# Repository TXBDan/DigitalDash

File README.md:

# DigitalDash

This is a prototype digital dashboard for use in motorsports. I made it in 2015 and successfully ran it in my track car for a couple years. I'm now archiving the project here.

It features:
* LPC4088 microcontroller
* Many-LED RGB sequential shift light
* 20x4 character LCD display
* 2 LEDs (power/status and alarm)
* 3 push buttons (change screen, select, option)
* 4 analog inputs (water temp, oil temp, oil pressure, throttle position)
* 2 speed/pulse inputs (speed and tach)
* 10Hz GPS (position and elevation)
* 3-axis accelerometer
* SDcard logging

For a lot more info, check out the blog here: https://projectsofdan.com/?cat=18

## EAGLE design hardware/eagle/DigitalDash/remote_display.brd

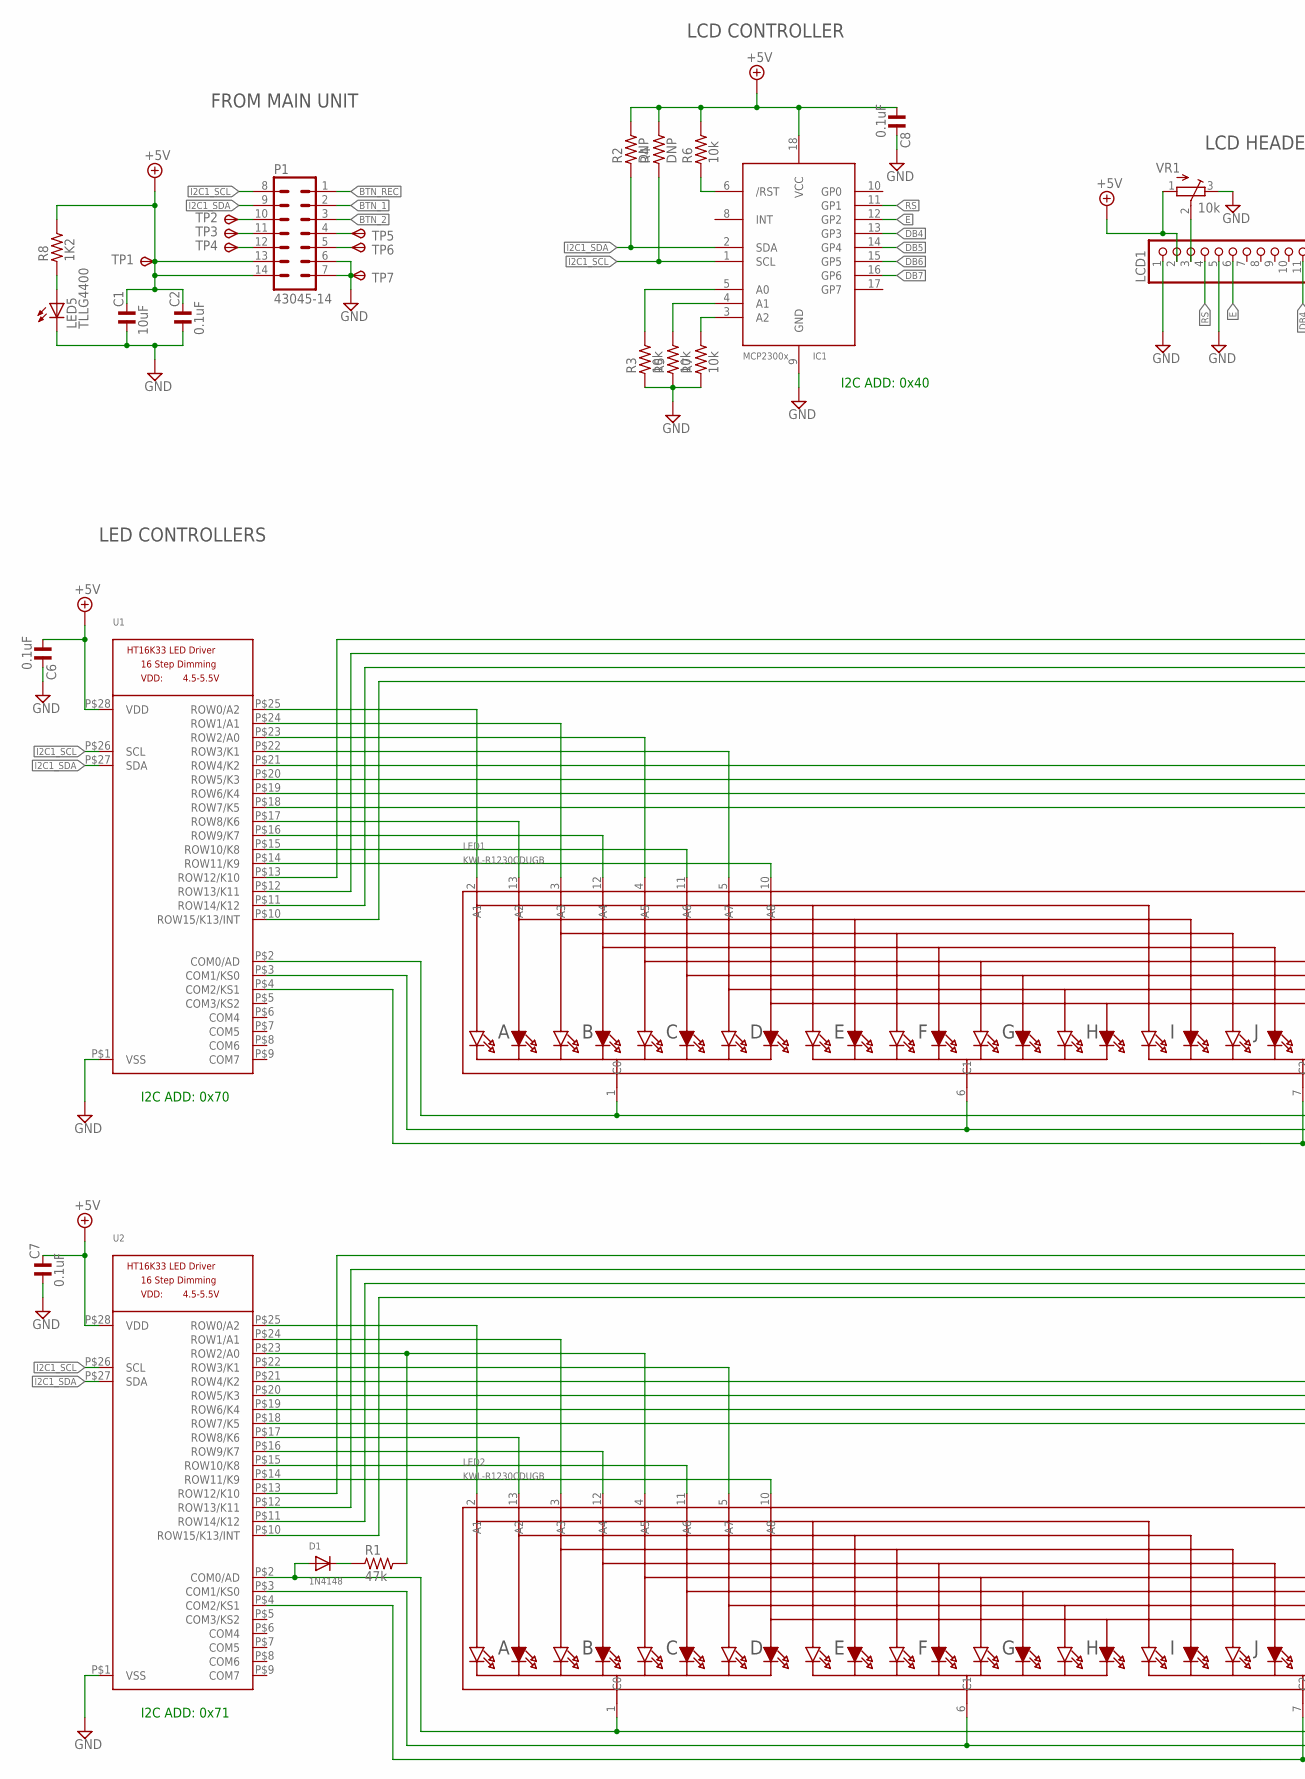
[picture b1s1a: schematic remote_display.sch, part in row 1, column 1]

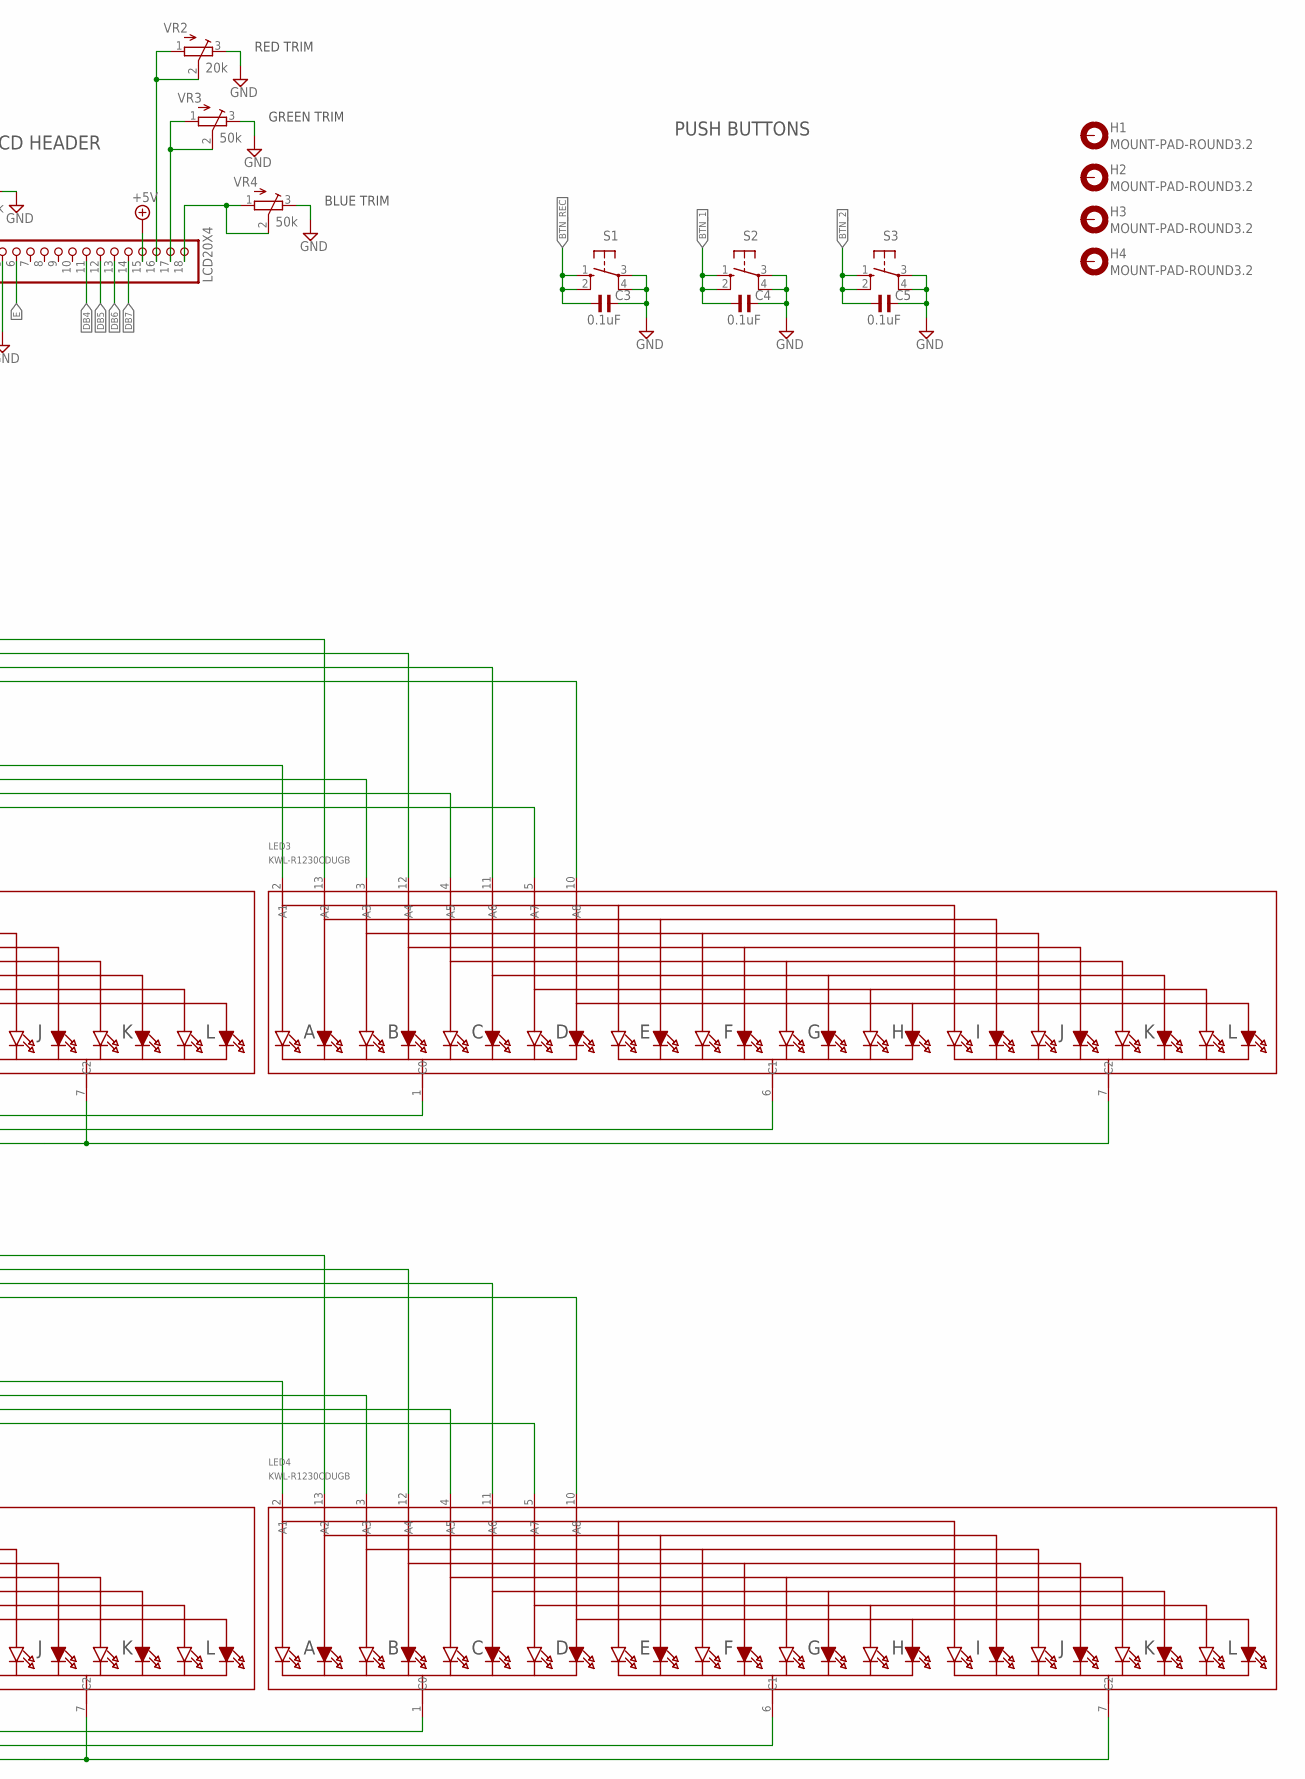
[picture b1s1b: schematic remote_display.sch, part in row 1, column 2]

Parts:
C1: 10uF; C0805; MPN C2012X5R1E106K125AB
C2, C3, C4, C5, C6, C7, C8: 0.1uF; C0805; MPN C2012X7R1H104K085AA
D1: 1N4148; SOD-323F; MPN MMBT2222ALT3G
H1, H2, H3, H4: MOUNT-PAD-ROUND3.2; 3,2-PAD
IC1: MCP2300X/SO; SO18W; MPN MCP23008-E/SO
LCD1: LCD20X4
LED1, LED2, LED3, LED4: KWL-R1230CDUGB; SEGMENT_BICOL_BL-AR12Z3010
LED5: TLLG4400; LED3MM; MPN TLLG4400
P1: 43045-14; MPN 43045-1400
R1: 47k; R0805; MPN CRCW080547K0FKEAHP
R2, R4: DNP; R0805; MPN CRCW080510K0FKTA
R3, R5, R6, R7: 10k; R0805; MPN CRCW080510K0FKTA
R8: 1K2; R0805; MPN CRCW080510K0FKTA
S1, S2, S3: 10-XX; B3F-10XX
TP1, TP2, TP3, TP4, TP5, TP6, TP7: TPSPAD1-13; P1-13
U1, U2: HT16K33_SOP28; SOP28_300MIL
VR1: 10k; TC33X; MPN TC33X-2-103E
VR2: 20k; TC33X; MPN TC33X-2-203E
VR3, VR4: 50k; TC33X; MPN TC33X-2-503E

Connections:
+5V: C1.2, C2.2, C6.1, C7.2, C8.1, IC1.18 (VCC), LCD1.2, LCD1.15, P1.13, P1.14, R2.2, R4.2, R6.2, R8.2, TP1.TP, U1.P$28 (VDD), U2.P$28 (VDD), VR1.1 (A)
BTN_1: C4.1, P1.2, S2.1 (S), S2.2 (S1)
BTN_2: C5.1, P1.3, S3.1 (S), S3.2 (S1)
BTN_REC: C3.1, P1.1, S1.1 (S), S1.2 (S1)
DB4: IC1.13 (GP3), LCD1.11
DB5: IC1.14 (GP4), LCD1.12
DB6: IC1.15 (GP5), LCD1.13
DB7: IC1.16 (GP6), LCD1.14
E: IC1.12 (GP2), LCD1.6
GND: C1.1, C2.1, C3.2, C4.2, C5.2, C6.2, C7.1, C8.2, IC1.9 (GND), LCD1.1, LCD1.5, LED5.K (C), P1.6, P1.7, R3.1, R5.1, R7.1, S1.3, S1.4 (P1), S2.3, S2.4 (P1), S3.3, S3.4 (P1), TP7.TP, U1.P$1 (VSS), U2.P$1 (VSS), VR1.3 (E), VR2.3 (E), VR3.3 (E), VR4.3 (E)
I2C1_SCL: IC1.1 (SCL), P1.8, R4.1, U1.P$26 (SCL), U2.P$26 (SCL)
I2C1_SDA: IC1.2 (SDA), P1.9, R2.1, U1.P$27 (SDA), U2.P$27 (SDA)
unnamed: LCD1.17, VR3.1 (A), VR3.2 (S)
unnamed: D1.C, R1.1
unnamed: LCD1.3, VR1.2 (S)
unnamed: IC1.3 (A2), R7.2
unnamed: IC1.4 (A1), R5.2
unnamed: LED1.2 (A1), U1.P$25 (ROW0/A2)
unnamed: LCD1.16, VR2.1 (A), VR2.2 (S)
unnamed: LED1.7 (C2), LED3.7 (C2), U1.P$4 (COM2/KS1)
unnamed: IC1.6 (/RST), R6.1
unnamed: LED5.A, R8.1
unnamed: LED1.1 (C0), LED3.1 (C0), U1.P$2 (COM0/AD)
unnamed: LED1.6 (C1), LED3.6 (C1), U1.P$3 (COM1/KS0)
unnamed: LED1.3 (A3), U1.P$24 (ROW1/A1)
unnamed: LED1.13 (A2), U1.P$17 (ROW8/K6)
unnamed: LED1.12 (A4), U1.P$16 (ROW9/K7)
unnamed: LED1.11 (A6), U1.P$15 (ROW10/K8)
unnamed: LED1.10 (A8), U1.P$14 (ROW11/K9)
unnamed: LED1.5 (A7), U1.P$22 (ROW3/K1)
unnamed: LED1.4 (A5), U1.P$23 (ROW2/A0)
unnamed: LED3.2 (A1), U1.P$21 (ROW4/K2)
unnamed: LED3.3 (A3), U1.P$20 (ROW5/K3)
unnamed: LED3.4 (A5), U1.P$19 (ROW6/K4)
unnamed: LED3.5 (A7), U1.P$18 (ROW7/K5)
unnamed: LED3.13 (A2), U1.P$13 (ROW12/K10)
unnamed: IC1.5 (A0), R3.2
unnamed: P1.5, TP6.TP
unnamed: LED3.12 (A4), U1.P$12 (ROW13/K11)
unnamed: LED3.11 (A6), U1.P$11 (ROW14/K12)
unnamed: LED3.10 (A8), U1.P$10 (ROW15/K13/INT)
unnamed: D1.A, LED2.1 (C0), LED4.1 (C0), U2.P$2 (COM0/AD)
unnamed: LED2.6 (C1), LED4.6 (C1), U2.P$3 (COM1/KS0)
unnamed: LED2.7 (C2), LED4.7 (C2), U2.P$4 (COM2/KS1)
unnamed: LED2.2 (A1), U2.P$25 (ROW0/A2)
unnamed: LED2.3 (A3), U2.P$24 (ROW1/A1)
unnamed: LED2.13 (A2), U2.P$17 (ROW8/K6)
unnamed: LED2.12 (A4), U2.P$16 (ROW9/K7)
unnamed: LED2.11 (A6), U2.P$15 (ROW10/K8)
unnamed: LCD1.18, VR4.1 (A), VR4.2 (S)
unnamed: LED2.10 (A8), U2.P$14 (ROW11/K9)
unnamed: LED2.5 (A7), U2.P$22 (ROW3/K1)
unnamed: LED2.4 (A5), R1.2, U2.P$23 (ROW2/A0)
unnamed: LED4.2 (A1), U2.P$21 (ROW4/K2)
unnamed: LED4.3 (A3), U2.P$20 (ROW5/K3)
unnamed: LED4.4 (A5), U2.P$19 (ROW6/K4)
unnamed: LED4.5 (A7), U2.P$18 (ROW7/K5)
unnamed: LED4.13 (A2), U2.P$13 (ROW12/K10)
unnamed: LED4.12 (A4), U2.P$12 (ROW13/K11)
unnamed: LED4.11 (A6), U2.P$11 (ROW14/K12)
unnamed: LED4.10 (A8), U2.P$10 (ROW15/K13/INT)
unnamed: P1.4, TP5.TP
unnamed: P1.12, TP4.TP
unnamed: P1.11, TP3.TP
unnamed: P1.10, TP2.TP
RS: IC1.11 (GP1), LCD1.4

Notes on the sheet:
I2C ADD: 0x70
I2C ADD: 0x71
I2C ADD: 0x40
FROM MAIN UNIT
LCD CONTROLLER
LCD HEADER
PUSH BUTTONS
LED CONTROLLERS
RED TRIM
GREEN TRIM
BLUE TRIM

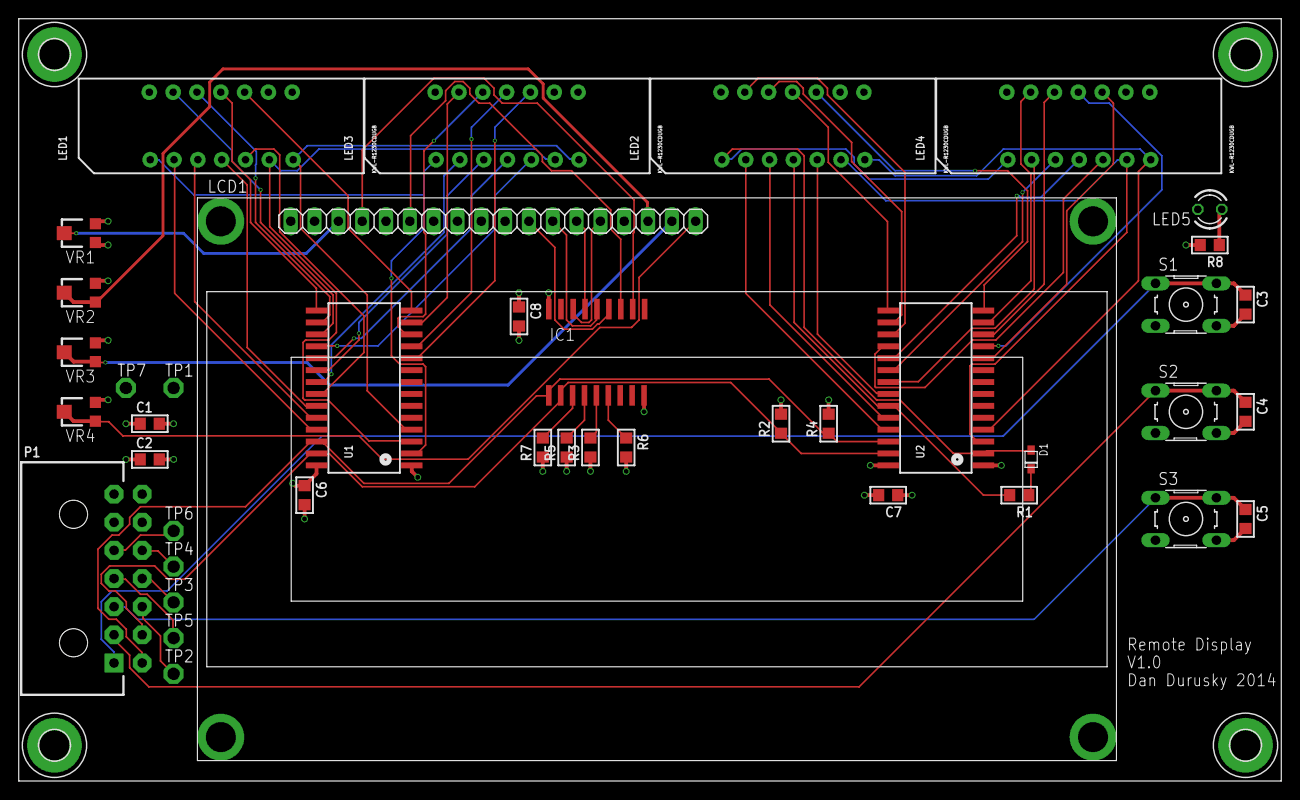
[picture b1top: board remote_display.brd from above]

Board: 4 copper layers, 134.6 x 81.3 mm, 45 parts (0 on the bottom side), 66 nets.

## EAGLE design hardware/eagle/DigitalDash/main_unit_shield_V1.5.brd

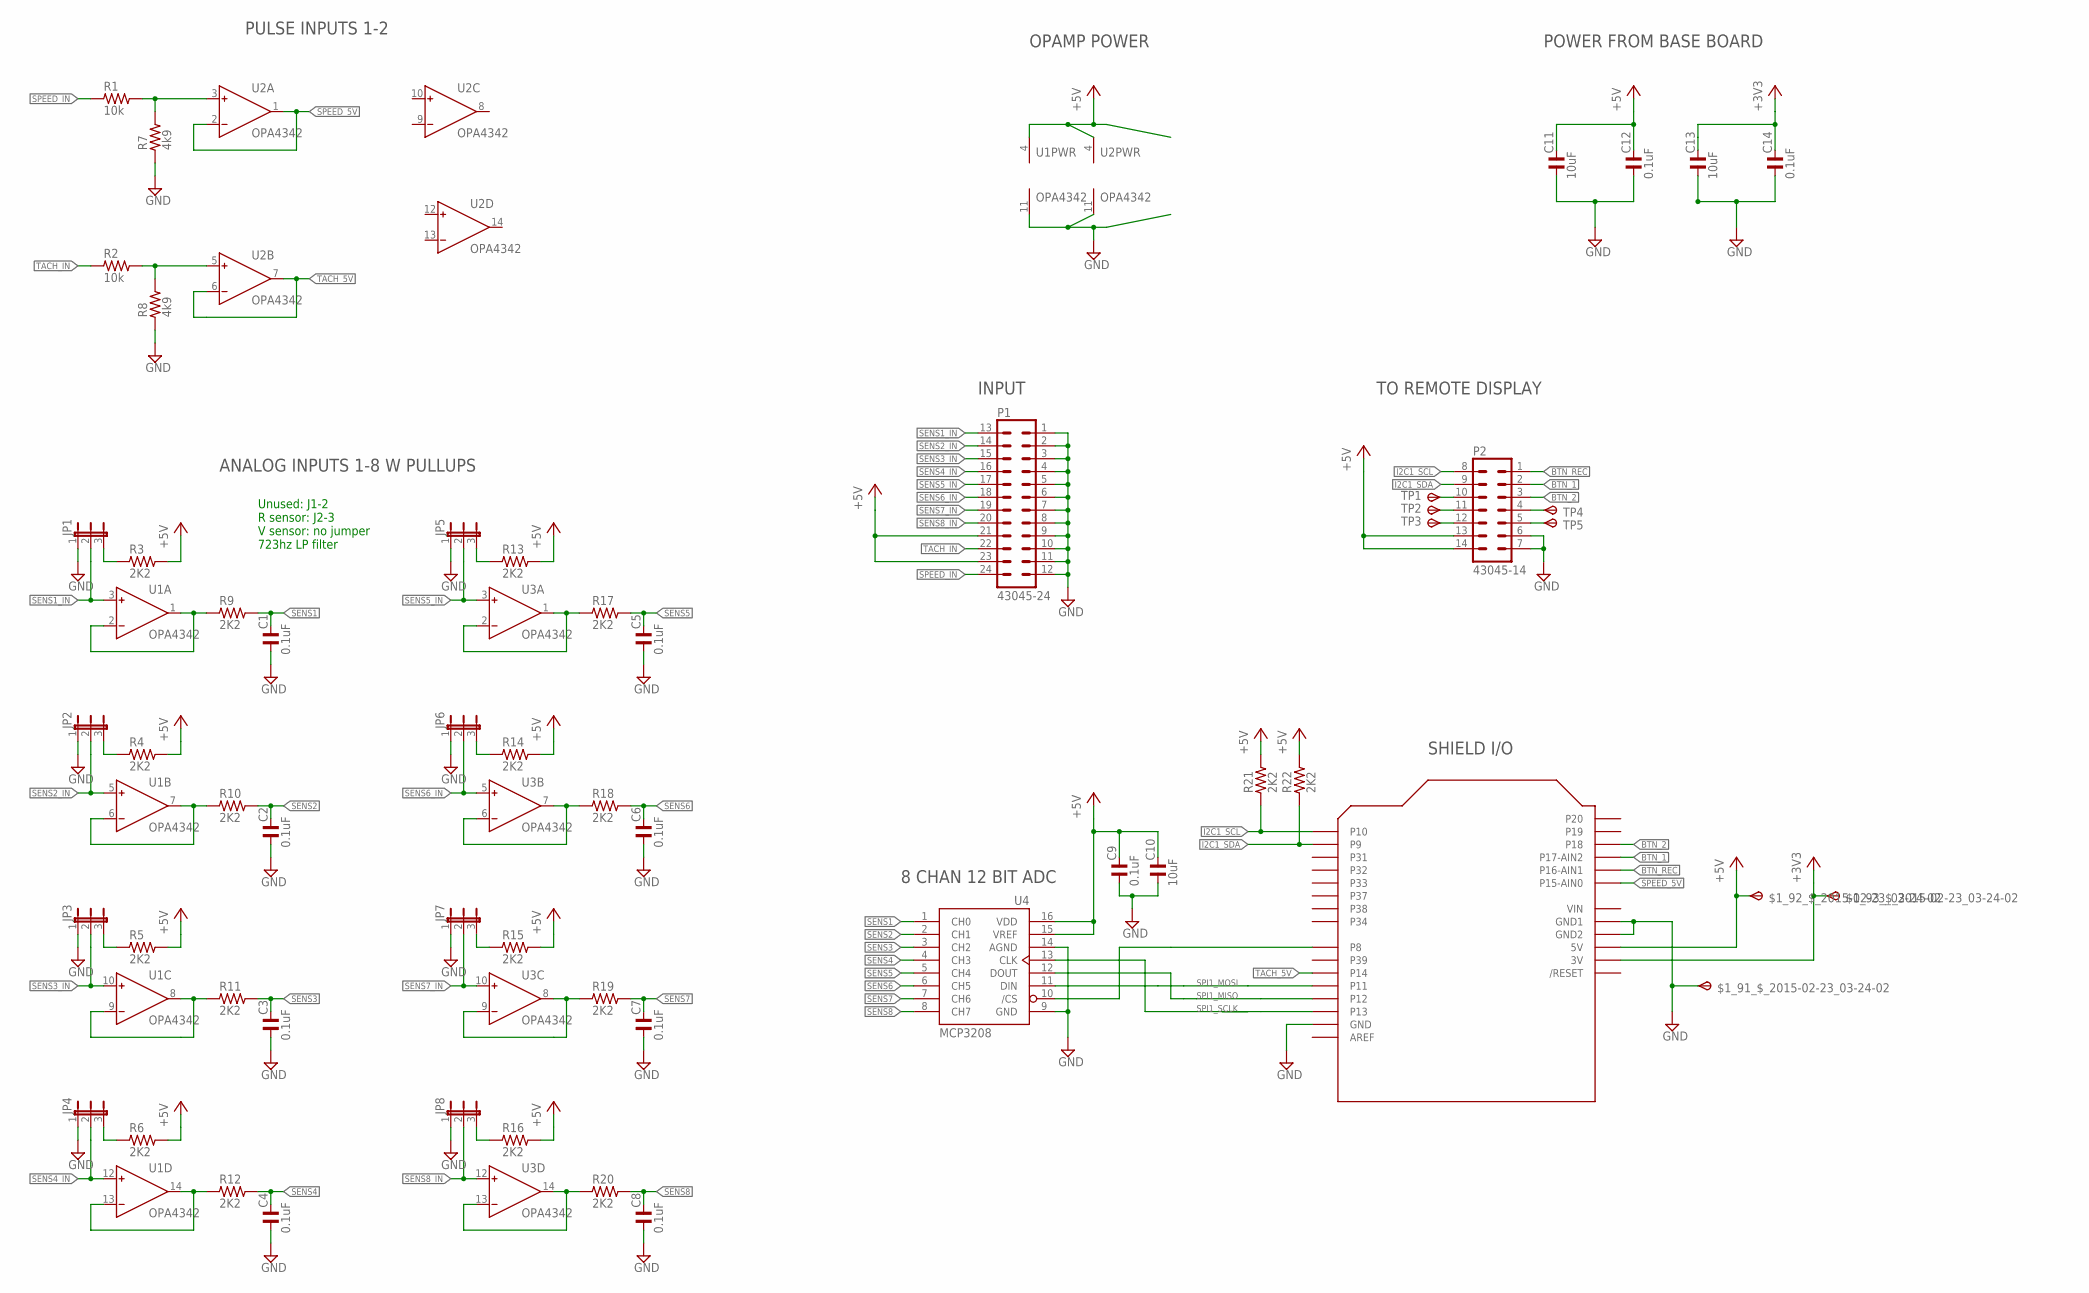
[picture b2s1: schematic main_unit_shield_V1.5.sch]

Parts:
$1_91_$_2015-02-23_03-24-02, $1_92_$_2015-02-23_03-24-02, $1_93_$_2015-02-23_03-24-02: TPSPAD1-13; P1-13
C1, C2, C3, C4, C5, C6, C7, C8, C9, C12, C14: 0.1uF; C0805; MPN C2012X7R1H104K085AA
C10, C11, C13: 10uF; C0805; MPN C2012X5R1E106K125AB
JP1, JP2, JP3, JP4, JP5, JP6, JP7, JP8: JP2E; JP2
P1: 43045-24; MPN 43045-2400
P2: 43045-14; MPN 43045-1400
R1: 10k; R0805; MPN CRCW08058K20FKEAHP
R2: 10k; R0805; MPN CRCW080520K0FKEA
R3, R4, R5, R6, R9, R10, R11, R12, R13, R14, R15, R16, R17, R18, R19, R20, R21, R22: 2K2; R0805; MPN CRCW08052K20FKEA
R7: 4k9; R0805; MPN CRCW080520K0FKEA
R8: 4k9; R0805; MPN CRCW08058K20FKEAHP
TP1, TP2, TP3, TP4, TP5: TPSPAD1-13; P1-13
U1, U2, U3: OPA4342; SO14
U4: MCP3208; SO16; MPN MCP3208-BI/SL
U6: ARDUINOUNO; ARDUINO

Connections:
+3V3: $1_93_$_2015-02-23_03-24-02.TP, C13.2, C14.2, U6.3V
+5V: $1_92_$_2015-02-23_03-24-02.TP, C9.2, C10.2, C11.2, C12.2, P1.21, P1.23, P2.13, P2.14, R3.2, R4.2, R5.2, R6.2, R13.2, R14.2, R15.2, R16.2, R21.2, R22.2, U1.4 (V+), U2.4 (V+), U4.15 (VREF), U4.16 (VDD), U6.5V
BTN_1: P2.2, U6.A2 (P17-AIN2)
BTN_2: P2.3, U6.A3 (P18)
BTN_REC: P2.1, U6.A1 (P16-AIN1)
GND: $1_91_$_2015-02-23_03-24-02.TP, C1.1, C2.1, C3.1, C4.1, C5.1, C6.1, C7.1, C8.1, C9.1, C10.1, C11.1, C12.1, C13.1, C14.1, JP1.1, JP2.1, JP3.1, JP4.1, JP5.1, JP6.1, JP7.1, JP8.1, P1.1, P1.2, P1.3, P1.4, P1.5, P1.6, P1.7, P1.8, P1.9, P1.10, P1.11, P1.12, P2.6, P2.7, R7.1, R8.1, U1.11 (V-), U2.11 (V-), U4.9 (GND), U4.14 (AGND), U6.GND, U6.GND1, U6.GND2
I2C1_SCL: P2.8, R21.1, U6.D0 (P10)
I2C1_SDA: P2.9, R22.1, U6.D1 (P9)
unnamed: R1.2, R7.2, U2.3 (IN+)
unnamed: JP1.3, R3.1
unnamed: R2.2, R8.2, U2.5 (IN+)
unnamed: JP2.3, R4.1
unnamed: JP3.3, R5.1
unnamed: U4.10 (/CS), U6.D8 (P8)
unnamed: JP5.3, R13.1
unnamed: JP4.3, R6.1
unnamed: JP6.3, R14.1
unnamed: JP7.3, R15.1
unnamed: JP8.3, R16.1
unnamed: R9.1, U1.1 (OUT), U1.2 (IN-)
unnamed: P2.10, TP1.TP
unnamed: P2.11, TP2.TP
unnamed: P2.12, TP3.TP
unnamed: P2.4, TP4.TP
unnamed: P2.5, TP5.TP
SENS1: C1.2, R9.2, U4.1 (CH0)
SENS1_BUF1: R17.1, U3.1 (OUT), U3.2 (IN-)
SENS1_IN: JP1.2, P1.13, U1.3 (IN+)
SENS2: C2.2, R10.2, U4.2 (CH1)
SENS2_BUF: R10.1, U1.6 (IN-), U1.7 (OUT)
SENS2_BUF1: R18.1, U3.6 (IN-), U3.7 (OUT)
SENS2_IN: JP2.2, P1.14, U1.5 (IN+)
SENS3: C3.2, R11.2, U4.3 (CH2)
SENS3_BUF: R11.1, U1.8 (OUT), U1.9 (IN-)
SENS3_BUF1: R19.1, U3.8 (OUT), U3.9 (IN-)
SENS3_IN: JP3.2, P1.15, U1.10 (IN+)
SENS4: C4.2, R12.2, U4.4 (CH3)
SENS4_BUF: R12.1, U1.13 (IN-), U1.14 (OUT)
SENS4_BUF1: R20.1, U3.13 (IN-), U3.14 (OUT)
SENS4_IN: JP4.2, P1.16, U1.12 (IN+)
SENS5: C5.2, R17.2, U4.5 (CH4)
SENS5_IN: JP5.2, P1.17, U3.3 (IN+)
SENS6: C6.2, R18.2, U4.6 (CH5)
SENS6_IN: JP6.2, P1.18, U3.5 (IN+)
SENS7: C7.2, R19.2, U4.7 (CH6)
SENS7_IN: JP7.2, P1.19, U3.10 (IN+)
SENS8: C8.2, R20.2, U4.8 (CH7)
SENS8_IN: JP8.2, P1.20, U3.12 (IN+)
SPEED_5V: U2.1 (OUT), U2.2 (IN-), U6.A0 (P15-AIN0)
SPEED_IN: P1.24, R1.1
SPI1_MISO: U4.12 (DOUT), U6.D12 (P12)
SPI1_MOSI: U4.11 (DIN), U6.D11 (P11)
SPI1_SCLK: U4.13 (CLK), U6.D13 (P13)
TACH_5V: U2.6 (IN-), U2.7 (OUT), U6.D10 (P14)
TACH_IN: P1.22, R2.1
V+: U3.4 (V+)
V-: U3.11 (V-)
VIN: U6.VIN

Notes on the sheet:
ANALOG INPUTS 1-8 W PULLUPS
PULSE INPUTS 1-2
TO REMOTE DISPLAY
SHIELD I/O
8 CHAN 12 BIT ADC
OPAMP POWER
POWER FROM BASE BOARD
INPUT
Unused: J1-2 R sensor: J2-3 V sensor: no jumper 723hz LP filter

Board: 4 copper layers, 59 parts (0 on the bottom side), 55 nets, no tracks yet.

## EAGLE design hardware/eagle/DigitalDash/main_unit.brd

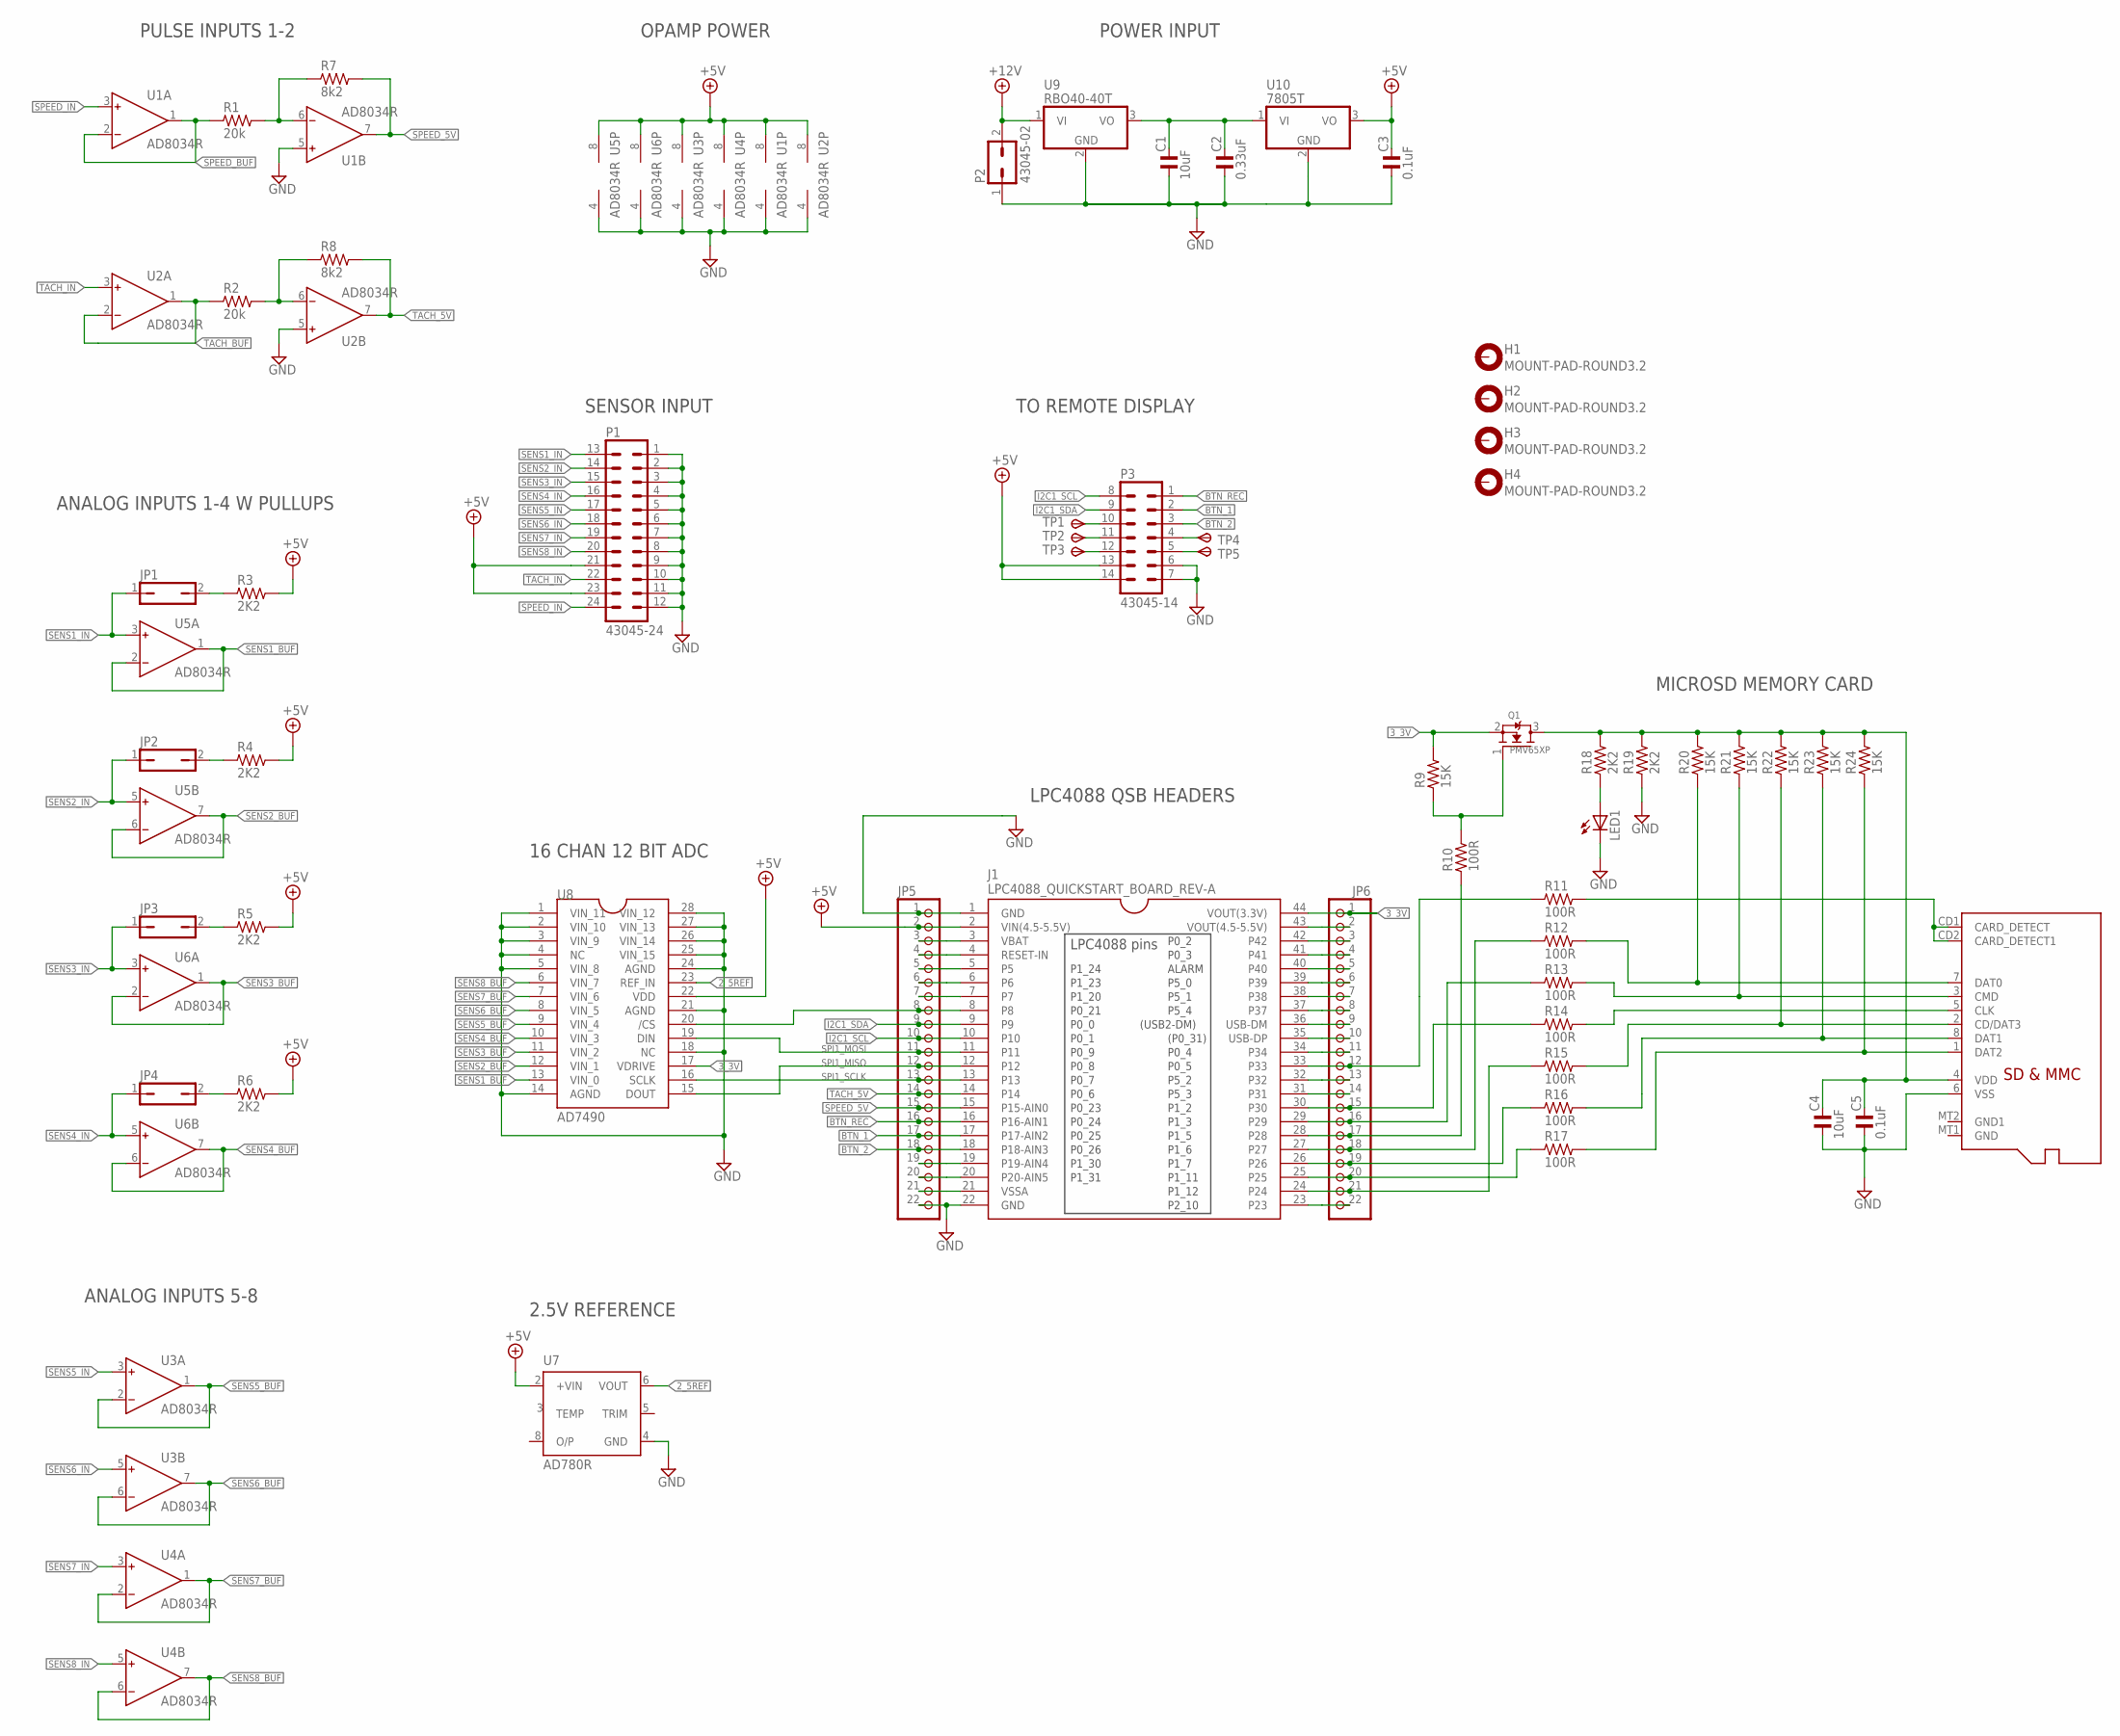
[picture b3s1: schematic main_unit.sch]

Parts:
C1, C4: 10uF; C0805
C2: 0.33uF; C0805
C3, C5: 0.1uF; C0805
H1, H2, H3, H4: MOUNT-PAD-ROUND3.2; 3,2-PAD
J1: LPC4088_QUICKSTART_BOARD_REV-A
JP1, JP2, JP3, JP4: JP1Q; JP1
JP5, JP6: PINHD-1X22; 1X22
LED1: LEDCHIP-LED0805; CHIP-LED0805
P1: 43045-24
P2: 43045-02
P3: 43045-14
Q1: PMV65XP; SOT23
R1, R2: 20k; R0805
R3, R4, R5, R6, R18, R19: 2K2; R0805
R7, R8: 8k2; R0805
R9, R20, R21, R22, R23, R24: 15K; R0805
R10, R11, R12, R13, R14, R15, R16, R17: 100R; R0805
SD1: MICROSD_SDMODE; MICROSD
TP1, TP2, TP3, TP4, TP5: TPSPAD1-13; P1-13
U1, U2, U3, U4, U5, U6: AD8034R; SO8
U7: AD780R; SO8
U8: AD7490; TSSOP28
U9: RBO40-40T; TO220H
U10: 7805T; TO220H

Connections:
2_5REF: U7.6 (VOUT), U8.23 (REF_IN)
3_3V: J1.44 (VOUT(3.3V)), JP6.1, Q1.2 (S), R9.2, U8.17 (VDRIVE)
+5V: C3.2, J1.2 (VIN(4.5-5.5V)), JP5.2, P1.21, P1.23, P3.13, P3.14, R3.2, R4.2, R5.2, R6.2, U1.8 (V+), U2.8 (V+), U3.8 (V+), U4.8 (V+), U5.8 (V+), U6.8 (V+), U7.2 (+VIN), U8.22 (VDD), U10.3 (VO)
+12V: P2.2, U9.1 (VI)
BTN_1: J1.17 (P17-AIN2), JP5.17, P3.2
BTN_2: J1.18 (P18-AIN3), JP5.18, P3.3
BTN_REC: J1.16 (P16-AIN1), JP5.16, P3.1
GND: C1.1, C2.1, C3.1, C4.1, C5.1, J1.1 (GND), J1.22 (GND), JP5.1, JP5.22, LED1.C, P1.1, P1.2, P1.3, P1.4, P1.5, P1.6, P1.7, P1.8, P1.9, P1.10, P1.11, P1.12, P2.1, P3.6, P3.7, R19.1, SD1.6 (VSS), U1.4 (V-), U1.5 (IN+), U2.4 (V-), U2.5 (IN+), U3.4 (V-), U4.4 (V-), U5.4 (V-), U6.4 (V-), U7.4 (GND), U8.1 (VIN_11), U8.2 (VIN_10), U8.3 (VIN_9), U8.4 (NC), U8.5 (VIN_8), U8.14 (AGND), U8.18 (NC), U8.21 (AGND), U8.24 (AGND), U8.25 (VIN_15), U8.26 (VIN_14), U8.27 (VIN_13), U8.28 (VIN_12), U9.2 (GND), U10.2 (GND)
I2C1_SCL: J1.10, JP5.10, P3.8
I2C1_SDA: J1.9, JP5.9, P3.9
unnamed: R1.2, R7.1, U1.6 (IN-)
unnamed: R12.2, R20.1, SD1.7 (DAT0)
unnamed: R2.2, R8.1, U2.6 (IN-)
unnamed: R13.2, R21.1, SD1.3 (CMD)
unnamed: R14.2, SD1.5 (CLK)
unnamed: J1.8, JP5.8, U8.20 (/CS)
unnamed: R15.2, R22.1, SD1.2 (CD/DAT3)
unnamed: R16.2, R23.1, SD1.8 (DAT1)
unnamed: R17.2, R24.1, SD1.1 (DAT2)
unnamed: JP1.2, R3.1
unnamed: J1.27, JP6.18, R12.1
unnamed: J1.29, JP6.16, R13.1
unnamed: J1.30, JP6.15, R14.1
unnamed: J1.26, JP6.19, R16.1
unnamed: J1.25, JP6.20, R17.1
unnamed: J1.24, JP6.21, R15.1
unnamed: J1.28, JP6.17, R10.1
unnamed: Q1.1 (G), R9.1, R10.2
unnamed: LED1.A, R18.1
unnamed: R11.2, SD1.CD1 (CARD_DETECT), SD1.CD2 (CARD_DETECT1)
unnamed: JP3.2, R5.1
unnamed: J1.38, JP6.7
unnamed: P3.10, TP1.TP
unnamed: P3.11, TP2.TP
unnamed: JP2.2, R4.1
unnamed: C1.2, C2.2, U9.3 (VO), U10.1 (VI)
unnamed: P3.12, TP3.TP
unnamed: J1.3 (VBAT), JP5.3
unnamed: JP4.2, R6.1
unnamed: J1.4 (RESET-IN), JP5.4
unnamed: P3.4, TP4.TP
unnamed: J1.5, JP5.5
unnamed: J1.6, JP5.6
unnamed: P3.5, TP5.TP
unnamed: J1.7, JP5.7
unnamed: J1.19 (P19-AIN4), JP5.19
unnamed: J1.20 (P20-AIN5), JP5.20
unnamed: J1.21 (VSSA), JP5.21
unnamed: J1.43 (VOUT(4.5-5.5V)), JP6.2
unnamed: J1.42, JP6.3
unnamed: J1.41, JP6.4
unnamed: J1.40, JP6.5
unnamed: J1.39, JP6.6
unnamed: J1.37, JP6.8
unnamed: J1.36 (USB-DM), JP6.9
unnamed: J1.35 (USB-DP), JP6.10
unnamed: J1.34, JP6.11
unnamed: J1.33, JP6.12, R11.1
unnamed: J1.32, JP6.13
unnamed: J1.31, JP6.14
unnamed: J1.23, JP6.22
SENS1_BUF: U5.1 (OUT), U5.2 (IN-), U8.13 (VIN_0)
SENS1_IN: JP1.1, P1.13, U5.3 (IN+)
SENS2_BUF: U5.6 (IN-), U5.7 (OUT), U8.12 (VIN_1)
SENS2_IN: JP2.1, P1.14, U5.5 (IN+)
SENS3_BUF: U6.1 (OUT), U6.2 (IN-), U8.11 (VIN_2)
SENS3_IN: JP3.1, P1.15, U6.3 (IN+)
SENS4_BUF: U6.6 (IN-), U6.7 (OUT), U8.10 (VIN_3)
SENS4_IN: JP4.1, P1.16, U6.5 (IN+)
SENS5_BUF: U3.1 (OUT), U3.2 (IN-), U8.9 (VIN_4)
SENS5_IN: P1.17, U3.3 (IN+)
SENS6_BUF: U3.6 (IN-), U3.7 (OUT), U8.8 (VIN_5)
SENS6_IN: P1.18, U3.5 (IN+)
SENS7_BUF: U4.1 (OUT), U4.2 (IN-), U8.7 (VIN_6)
SENS7_IN: P1.19, U4.3 (IN+)
SENS8_BUF: U4.6 (IN-), U4.7 (OUT), U8.6 (VIN_7)
SENS8_IN: P1.20, U4.5 (IN+)
SPEED_5V: J1.15 (P15-AIN0), JP5.15, R7.2, U1.7 (OUT)
SPEED_BUF: R1.1, U1.1 (OUT), U1.2 (IN-)
SPEED_IN: P1.24, U1.3 (IN+)
SPI1_MISO: J1.12, JP5.12, U8.15 (DOUT)
SPI1_MOSI: J1.11, JP5.11, U8.19 (DIN)
SPI1_SCLK: J1.13, JP5.13, U8.16 (SCLK)
TACH_5V: J1.14, JP5.14, R8.2, U2.7 (OUT)
TACH_BUF: R2.1, U2.1 (OUT), U2.2 (IN-)
TACH_IN: P1.22, U2.3 (IN+)
VDD: C4.2, C5.2, Q1.3 (D), R18.2, R19.2, R20.2, R21.2, R22.2, R23.2, R24.2, SD1.4 (VDD)

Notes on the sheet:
ANALOG INPUTS 1-4 W PULLUPS
PULSE INPUTS 1-2
TO REMOTE DISPLAY
LPC4088 QSB HEADERS
MICROSD MEMORY CARD
16 CHAN 12 BIT ADC
2.5V REFERENCE
OPAMP POWER
POWER INPUT
ANALOG INPUTS 5-8
SENSOR INPUT

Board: 4 copper layers, 61 parts (0 on the bottom side), 87 nets, no tracks yet.

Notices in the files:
parts and their libraries:
con-molex-micro-fit: Copyright (C) 2011, Bob Starr
rc-master-smd: Copyright (C) 2007-2008, Bob Starr
